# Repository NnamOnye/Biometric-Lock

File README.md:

ESP-IDF APP
Created by: Nnam Onye
====================

# This is a biometric lock utilizing PIN, and a Finger Print Scanning module.
# This project is already optimized to a certain degree, it can already ask for pin/finger input on first start up + setup
# Has memory to store user pin and finger check and authenticate using memory.
# It can be expanded to save up to as many finger prints and passwords the engineer/designer/user wants.
# The PCB is designed using the same concept as one of my other projects, "keypadPCB" but with additions for the bolt lock,etc..
# I designed the hardware using KiCAD an ECAD Software

# Eclispe Download --> https://eclipseide.org/
# KiCAD Download --> https://www.kicad.org/download/

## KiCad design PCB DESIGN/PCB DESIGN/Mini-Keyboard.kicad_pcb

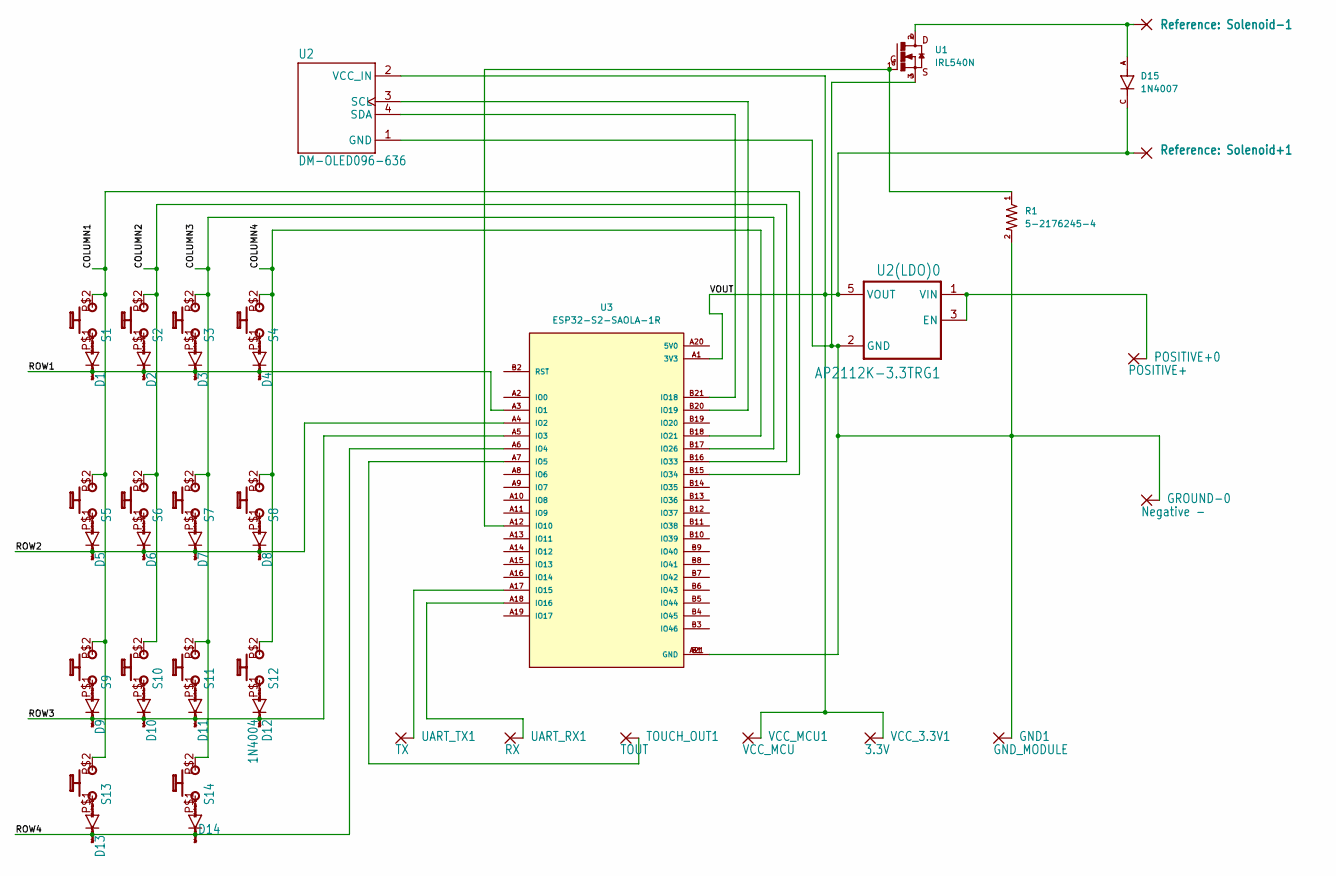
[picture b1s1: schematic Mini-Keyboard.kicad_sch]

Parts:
D1, D2, D3, D4, D5, D6, D7, D8, D9, D10, D11, D12, D13, D14: 1N4004; DO41-10_210
D15: 1N4007; DIOAD1060W80L520D270; PARTREV G
GND1: GND_MODULE; SMD2,54-5,08_412
GROUND-0: Negative -; SMD2,54-5,08_412
POSITIVE+0: POSITIVE+; SMD2,54-5,08_412
R1: 5-2176245-4; RESC3115X65N
S1, S2, S3, S4, S5, S6, S7, S8, S9, S10, S11, S12, S13, S14: MX1A-11NN; CHERRY_MX1A-11NN_SWITCH
Solenoid+1: Solenoid+1; SMD2,54-5,08_412
Solenoid-1: Solenoid-1; SMD2,54-5,08_412
TOUCH_OUT1: TOUT; SMD2,54-5,08_412
U1: IRL540N; TO220V
U2: DM-OLED096-636; MODULE_DM-OLED096-636
U2(LDO)0: AP2112K-3.3TRG1; SOT95P285X140-5N
U3: ESP32-S2-SAOLA-1R; XCVR_ESP32-S2-SAOLA-1R; PARTREV 1.2
UART_RX1: RX; SMD2,54-5,08_412
UART_TX1: TX; SMD2,54-5,08_412
VCC_3.3V1: 3.3V; SMD2,54-5,08_412
VCC_MCU1: VCC_MCU; SMD2,54-5,08_412

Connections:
/COLUMN1: S1.P$2 (S), S5.P$2 (S), S9.P$2 (S), S13.P$2 (S), U3.B15 (IO34)
/COLUMN2: S2.P$2 (S), S6.P$2 (S), S10.P$2 (S), U3.B16 (IO33)
/COLUMN3: S3.P$2 (S), S7.P$2 (S), S11.P$2 (S), S14.P$2 (S), U3.B17 (IO26)
/COLUMN4: S4.P$2 (S), S8.P$2 (S), S12.P$2 (S), U3.B18 (IO21)
/ROW1: D1.C, D2.C, D3.C, D4.C, U3.A3 (IO1)
/ROW2: D5.C, D6.C, D7.C, D8.C, U3.A4 (IO2)
/ROW3: D9.C, D10.C, D11.C, D12.C, U3.A5 (IO3)
/ROW4: D13.C, D14.C, U3.A6 (IO4)
/VOUT: D15.C, Solenoid+1.1, U2.2 (VCC_IN), U2(LDO)0.5 (VOUT), U3.A1 (3V3), VCC_3.3V1.1, VCC_MCU1.1
unnamed: GND1.1, GROUND-0.1, R1.2, U1.3, U2.1 (GND), U2(LDO)0.2 (GND), U3.A21 (GND), U3.B1 (GND)
unnamed: POSITIVE+0.1, U2(LDO)0.1 (VIN), U2(LDO)0.3 (EN)
unnamed: D1.A, S1.P$1
unnamed: D2.A, S2.P$1
unnamed: D3.A, S3.P$1
unnamed: D4.A, S4.P$1
unnamed: D5.A, S5.P$1
unnamed: D6.A, S6.P$1
unnamed: D7.A, S7.P$1
unnamed: D8.A, S8.P$1
unnamed: D9.A, S9.P$1
unnamed: D10.A, S10.P$1
unnamed: D11.A, S11.P$1
unnamed: D12.A, S12.P$1
unnamed: D13.A, S13.P$1
unnamed: D14.A, S14.P$1
unnamed: D15.A, Solenoid-1.1, U1.2
unnamed: TOUCH_OUT1.1, U3.A7 (IO5)
unnamed: U2.3 (SCL), U3.B20 (IO19)
unnamed: U2.4 (SDA), U3.B21 (IO18)
unnamed: R1.1, U1.1, U3.A12 (IO10)
unnamed: U3.A17 (IO15), UART_TX1.1
unnamed: U3.A18 (IO16), UART_RX1.1

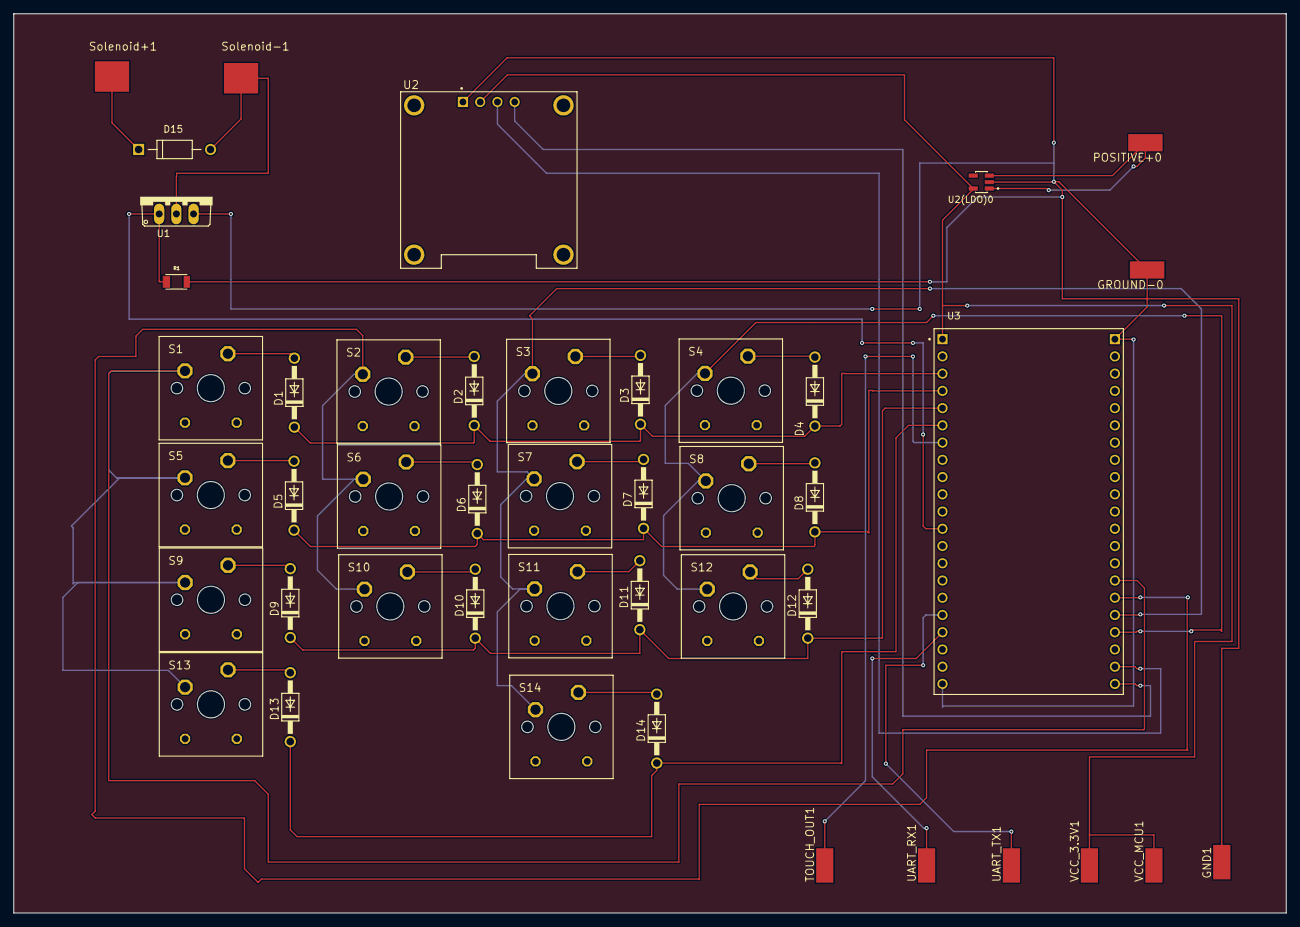
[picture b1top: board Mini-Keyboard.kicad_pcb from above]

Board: 2 copper layers, 187.5 x 132.5 mm, 44 parts (0 on the bottom side), 32 nets.

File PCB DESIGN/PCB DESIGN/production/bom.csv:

Designator,Footprint,Quantity,Value,LCSC Part #
"D1, D10, D11, D12, D13, D14, D2, D3, D4, D5, D6, D7, D8, D9",DO41-10_210,14,1N4004,
D15,DIOAD1060W80L520D270,1,1N4007,
GND1,"SMD2,54-5,08_412",1,GND_MODULE,
GROUND-0,"SMD2,54-5,08_412",1,Negative -,
POSITIVE+0,"SMD2,54-5,08_412",1,POSITIVE+,
R1,RESC3115X65N,1,5-2176245-4,
"S1, S10, S11, S12, S13, S14, S2, S3, S4, S5, S6, S7, S8, S9",CHERRY_MX1A-11NN_SWITCH,14,MX1A-11NN,
SOLENOID+1,"SMD2,54-5,08_412",1,Solenoid+1,
SOLENOID-1,"SMD2,54-5,08_412",1,Solenoid-1,
TOUCH_OUT1,"SMD2,54-5,08_412",1,TOUT,
U1,TO220V,1,IRL540N,
U2,MODULE_DM-OLED096-636,1,DM-OLED096-636,
U2(LDO)0,SOT95P285X140-5N,1,AP2112K-3.3TRG1,
U3,XCVR_ESP32-S2-SAOLA-1R,1,ESP32-S2-SAOLA-1R,
UART_RX1,"SMD2,54-5,08_412",1,RX,
UART_TX1,"SMD2,54-5,08_412",1,TX,
VCC_3.3V1,"SMD2,54-5,08_412",1,3.3V,
VCC_MCU1,"SMD2,54-5,08_412",1,VCC_MCU,

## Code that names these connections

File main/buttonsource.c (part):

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}

// Define row GPIO pins
#define ROW1_GPIO GPIO_NUM_1
#define ROW2_GPIO GPIO_NUM_2
#define ROW3_GPIO GPIO_NUM_3
#define ROW4_GPIO GPIO_NUM_4


// Define column GPIO pins
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void configure_buttons() {
	//Row Configuration
    gpio_config_t row1_conf = {
    .pin_bit_mask = (1ULL << ROW1_GPIO),
    .mode = GPIO_MODE_INPUT,
    .pull_up_en = GPIO_PULLUP_ENABLE,
    .intr_type = GPIO_INTR_DISABLE
	};
	
	gpio_config_t row2_conf = {
	    .pin_bit_mask = (1ULL << ROW2_GPIO),
	    .mode = GPIO_MODE_INPUT,
	    .pull_up_en = GPIO_PULLUP_ENABLE,
	    .intr_type = GPIO_INTR_DISABLE
	};
	
	gpio_config_t row3_conf = {
	    .pin_bit_mask = (1ULL << ROW3_GPIO),
	    .mode = GPIO_MODE_INPUT,
	    .pull_up_en = GPIO_PULLUP_ENABLE,
	    .intr_type = GPIO_INTR_DISABLE
	};
	
	gpio_config_t row4_conf = {
	    .pin_bit_mask = (1ULL << ROW4_GPIO),
	    .mode = GPIO_MODE_INPUT,
	    .pull_up_en = GPIO_PULLUP_ENABLE,
	    .intr_type = GPIO_INTR_DISABLE
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        }

        // Check if any row is pressed (low level)
        if (gpio_get_level(ROW1_GPIO) == 0) {
            printf("Button in column %d, row 1 pressed\n", col);
        }
        if (gpio_get_level(ROW2_GPIO) == 0) {
            printf("Button in column %d, row 2 pressed\n", col);
        }
        if (gpio_get_level(ROW3_GPIO) == 0) {
            printf("Button in column %d, row 3 pressed\n", col);
        }
        if (gpio_get_level(ROW4_GPIO) == 0) {
            printf("Button in column %d, row 4 pressed\n", col);
        }
    }
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


#define WAKEUP_MASK  ((1ULL << ROW1_GPIO) | (1ULL << ROW2_GPIO) | (1ULL << ROW3_GPIO) | (1ULL << ROW4_GPIO) | \
                      (1ULL << COL1_GPIO) | (1ULL << COL2_GPIO) | (1ULL << COL3_GPIO) | (1ULL << COL4_GPIO)|(1ULL << TOUCHOUT_GPIO))
                      //This is a bitmask that includes all the GPIOs of the keypad matrix (rows and columns

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    for (int i = sleep_delay_sec; i > 0; i--) {
		
        // Check if any key GPIO is LOW (pressed)
        if ((gpio_get_level(ROW1_GPIO) == 0) || (gpio_get_level(ROW2_GPIO) == 0) || 
            (gpio_get_level(ROW3_GPIO) == 0) || (gpio_get_level(ROW4_GPIO) == 0) ||
            (gpio_get_level(COL1_GPIO) == 0) || (gpio_get_level(COL2_GPIO) == 0) ||
            (gpio_get_level(COL3_GPIO) == 0) || (gpio_get_level(COL4_GPIO) == 0)||(gpio_get_level(TOUCHOUT_GPIO) == 0)) {
            cancel_sleep = true;
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
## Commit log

2025-06-26 README.md
2025-06-26 LICENSE
2025-06-26 HARDWARE DESIGN
2025-07-25 Schematic screenshot.png
